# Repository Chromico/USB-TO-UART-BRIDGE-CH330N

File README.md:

# CH330N USB TO UART BRIDGE
An open source USB to UART converter based on the CH330N IC and designed in KiCad. It's open hardware! Do what you want with it :)

My website: https://tecknologg.website

# Front 

# Back

# Documentation

You can get the official documentation here: https://github.com/Chromico/USB-TO-UART-BRIDGE-CH330N/blob/main/documentation/CH330N%20USB%20TO%20UART%20BRIDGE%20Documentation.pdf

# Certification

# Contact

Need to contact me ? Just send me an email at nathan@tecknologg.website or tecknologg@gmail.com

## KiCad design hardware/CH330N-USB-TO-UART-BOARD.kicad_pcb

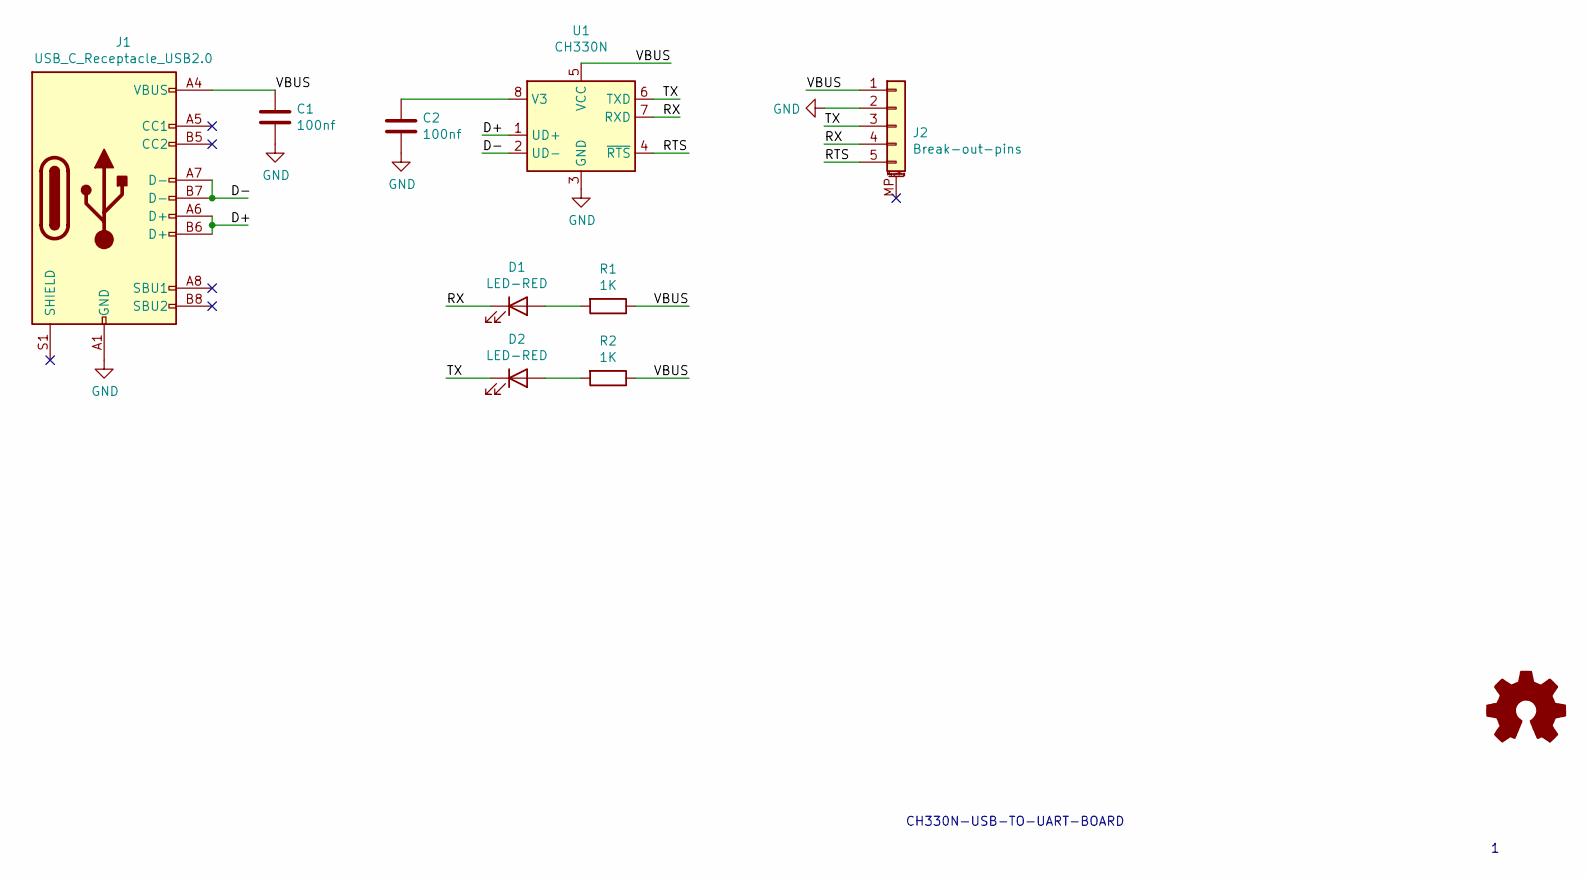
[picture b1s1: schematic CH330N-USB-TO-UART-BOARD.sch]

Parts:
C1, C2: 100nf
D1, D2: LED-RED
J1: USB_C_Receptacle_USB2.0
J2: Break-out-pins
R1, R2: 1K
U1: CH330N; SOIC-8_3.9x4.9mm_P1.27mm

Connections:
/D+: J1.A6 (D+), J1.B6 (D+), U1.1 (UD+)
/D-: J1.A7 (D-), J1.B7 (D-), U1.2 (UD-)
/RTS: J2.5, U1.4 (~RTS)
/RX: D1.1 (K), J2.4, U1.7 (RXD)
/TX: D2.1 (K), J2.3, U1.6 (TXD)
/VBUS: C1.1, J1.A4 (VBUS), J1.A9 (VBUS), J1.B4 (VBUS), J1.B9 (VBUS), J2.1, R1.1, R2.1, U1.5 (VCC)
GND: C1.2, C2.2, J1.A1 (GND), J1.A12 (GND), J1.B1 (GND), J1.B12 (GND), J2.2, U1.3 (GND)
unnamed: C2.1, U1.8 (V3)
unnamed: D1.2 (A), R1.2
unnamed: D2.2 (A), R2.2

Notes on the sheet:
CH330N-USB-TO-UART-BOARD

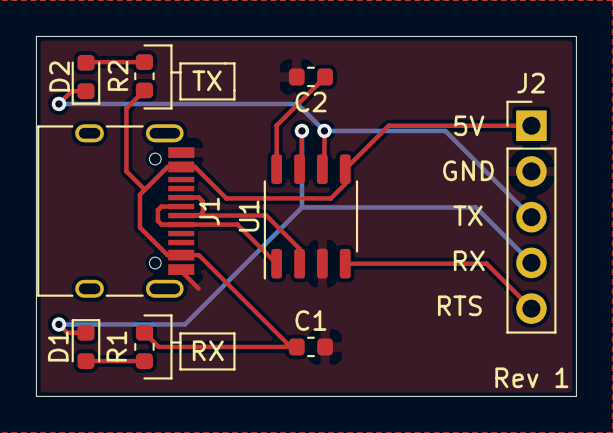
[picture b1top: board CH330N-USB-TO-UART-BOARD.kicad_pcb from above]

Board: 2 copper layers, 30.0 x 20.0 mm, 9 parts (0 on the bottom side), 10 nets.

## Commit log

2021-03-30 Create LICENSE
2021-03-30 [ImgBot] Optimize images
    *Total -- 458.98kb -> 411.96kb (10.24%)
    /photos/banner.png -- 336.23kb -> 295.98kb (11.97%)
    /photos/front.png -- 62.86kb -> 57.04kb (9.26%)
    /photos/back.png -- 59.89kb -> 58.94kb (1.58%)
